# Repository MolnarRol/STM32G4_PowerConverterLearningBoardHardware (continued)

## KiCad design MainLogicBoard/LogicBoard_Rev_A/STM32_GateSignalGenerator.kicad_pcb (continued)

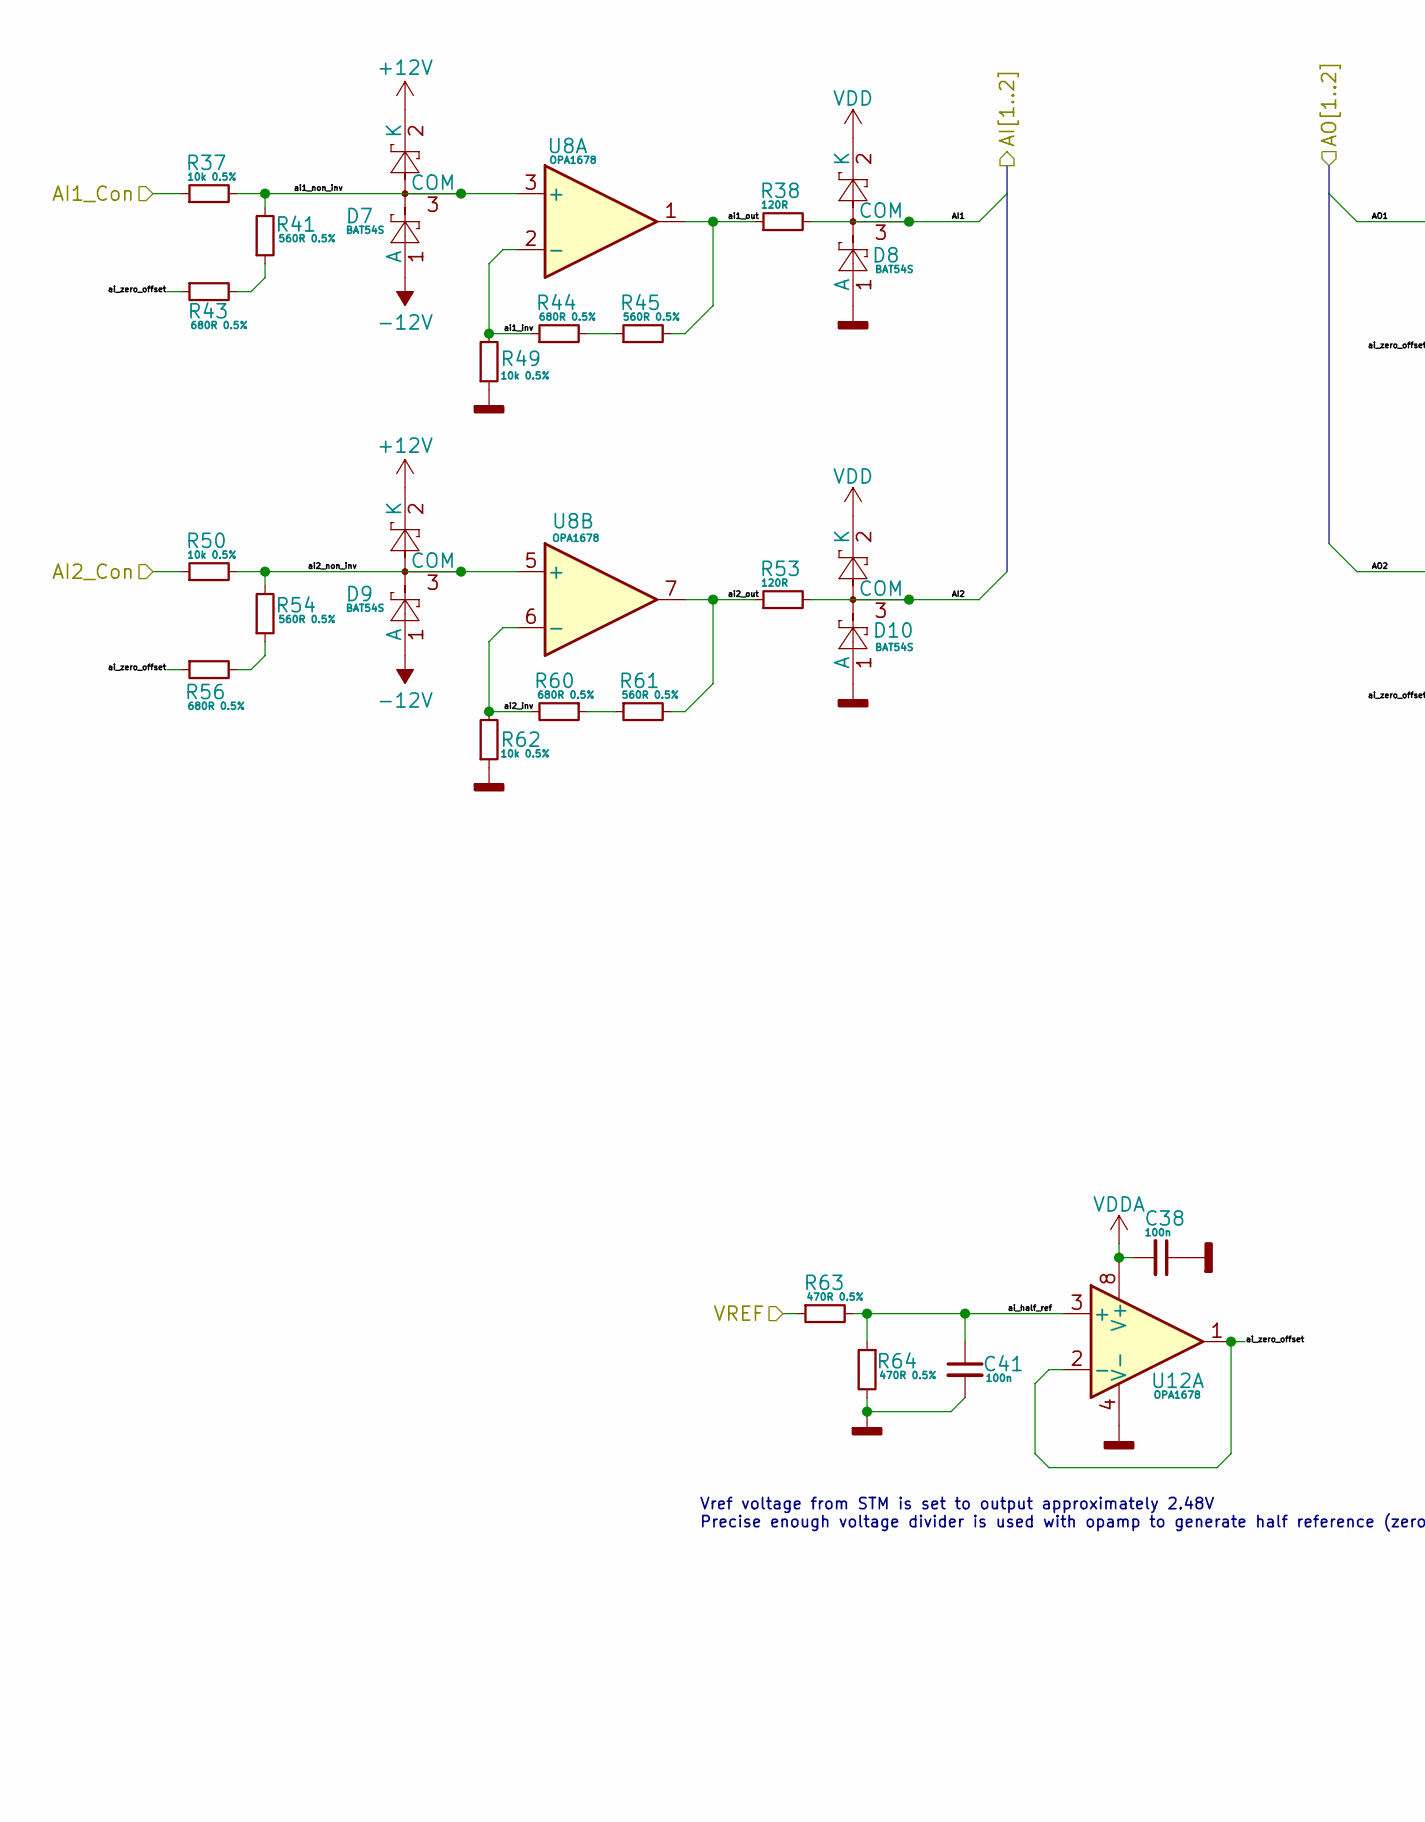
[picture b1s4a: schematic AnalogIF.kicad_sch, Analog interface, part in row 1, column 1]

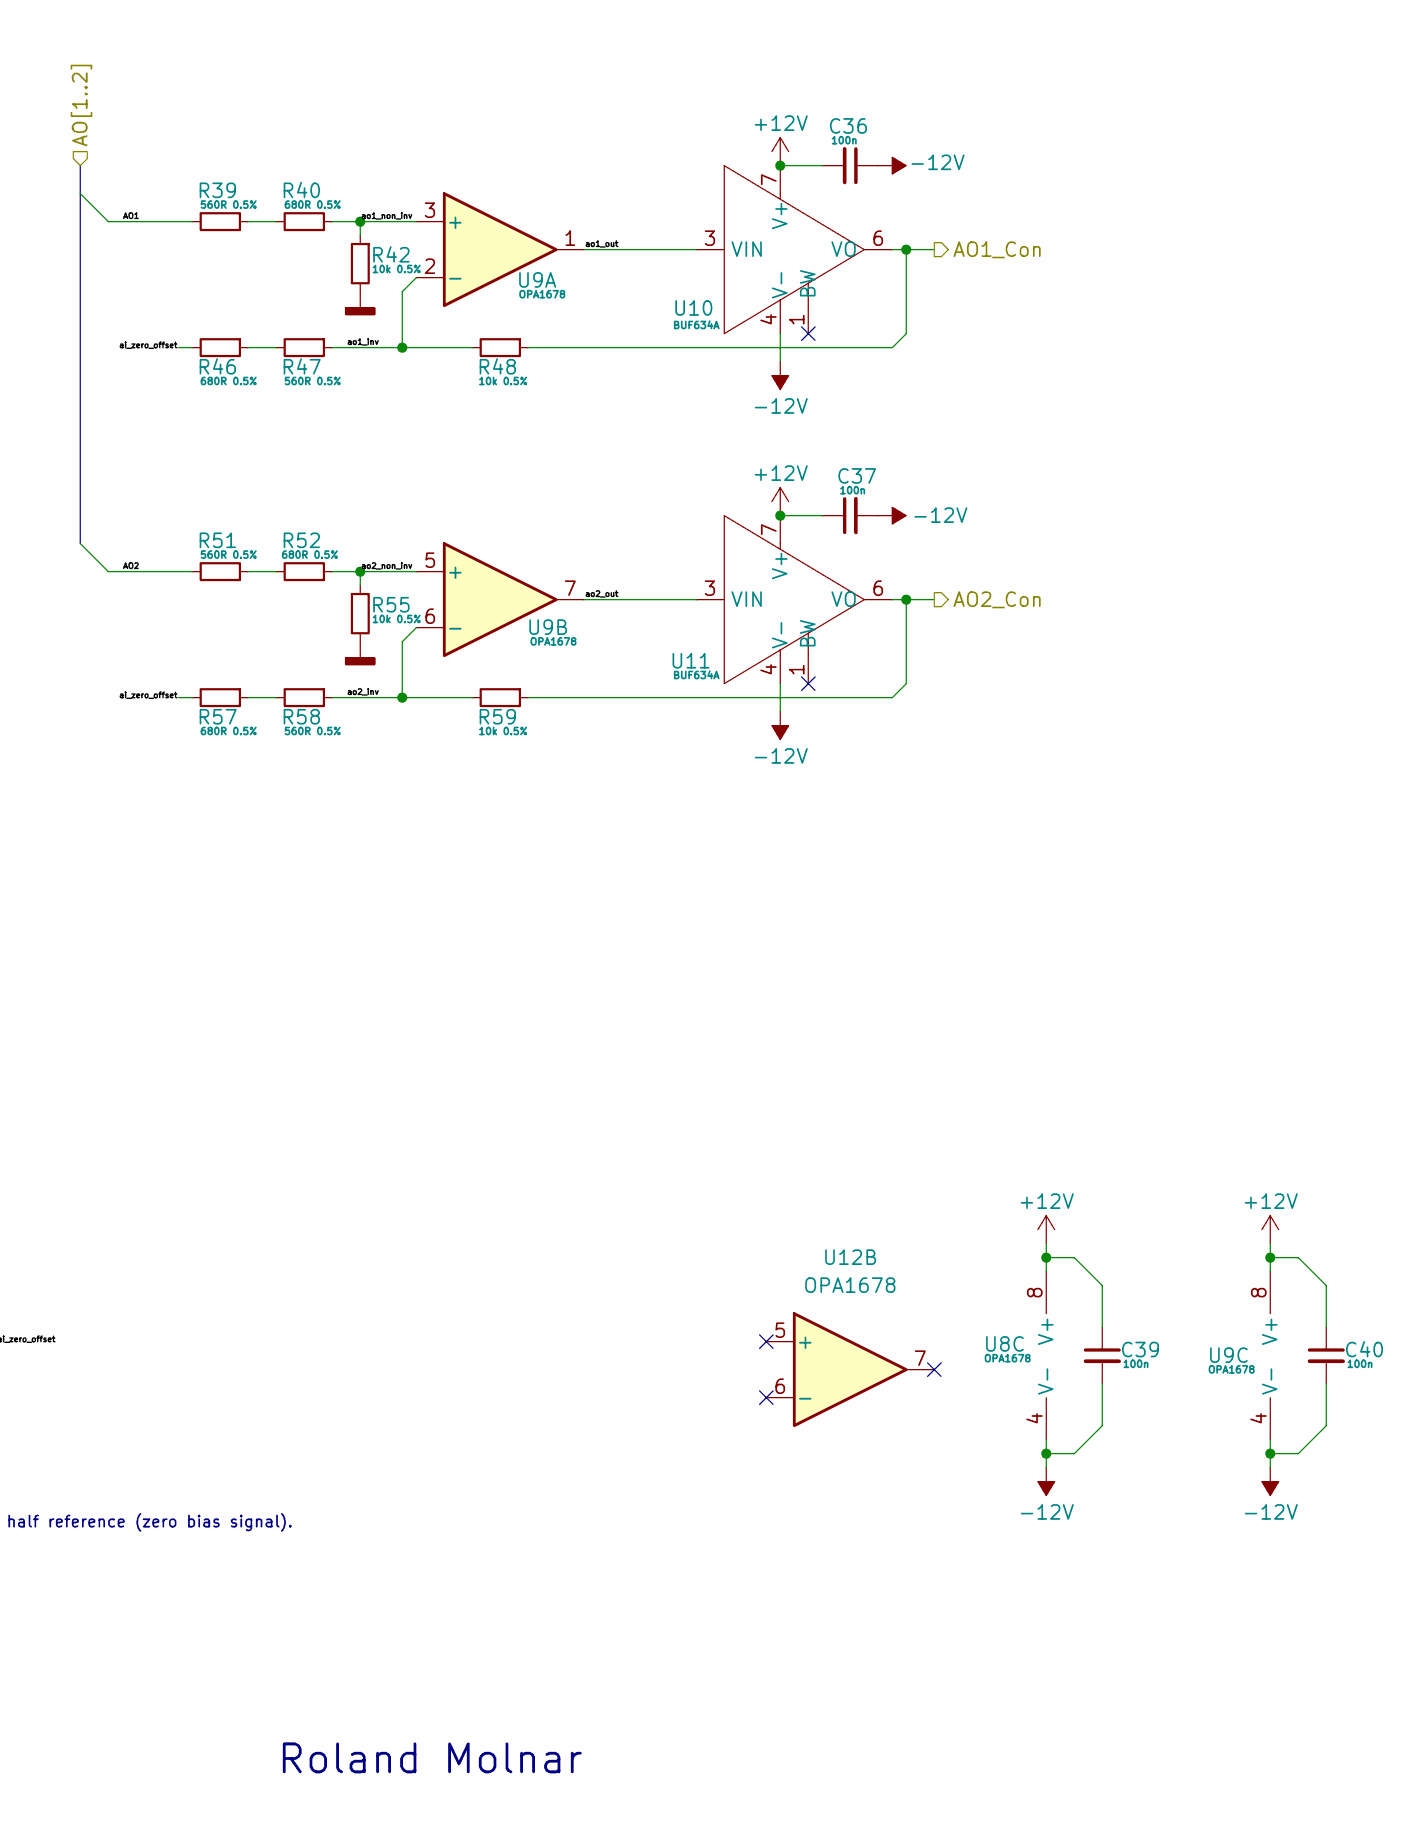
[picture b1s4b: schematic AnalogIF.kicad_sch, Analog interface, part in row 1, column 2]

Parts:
C36, C37, C38, C39, C40, C41: 100n; C_0805_2012Metric; Manufacturer PN C0805C104K5RAC7411; DigiKey PN 399-C0805C104K5RAC7210CT-ND
D7, D8, D9, D10: BAT54S; SOT-23; Manufacturer PN BAT54S; DigiKey PN 4878-BAT54SCT-ND
R37, R42, R48, R49, R50, R55, R59, R62: 10k 0.5%; R_0805_2012Metric; Manufacturer PN RT0805DRD0710KL; DigiKey PN 311-2699-1-ND
R38, R53: 120R; R_0805_2012Metric; Manufacturer PN RC0805FR-07120RL; DigiKey PN 311-120CRCT-ND
R39, R41, R45, R47, R51, R54, R58, R61: 560R 0.5%; R_0805_2012Metric; Manufacturer PN ERJ-PB6D5600V; DigiKey PN P20990CT-ND
R40, R43, R44, R46, R52, R56, R57, R60: 680R 0.5%; R_0805_2012Metric; Manufacturer PN ERJ-PB6D6800V; DigiKey PN P21000CT-ND
R63, R64: 470R 0.5%; R_0805_2012Metric; Manufacturer PN ESR10EZPD4700; DigiKey PN 846-ESR10EZPD4700CT-ND
U8, U9, U12: OPA1678; SOIC-8_3.9x4.9mm_P1.27mm; Manufacturer PN OPA1678IDR; DigiKey PN 296-47347-1-ND
U10, U11: BUF634A; SOIC-8_3.9x4.9mm_P1.27mm; Manufacturer PN BUF634AIDR; DigiKey PN 296-53619-1-ND

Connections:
+12V: C36.2, C37.1, C39.1, C40.1, D7.2 (K), D9.2 (K), U8.8 (V+), U9.8 (V+), U10.7 (V+), U11.7 (V+); also elsewhere on the board
-12V: C36.1, C37.2, C39.2, C40.2, D7.1 (A), D9.1 (A), U8.4 (V-), U9.4 (V-), U10.4 (V-), U11.4 (V-); also elsewhere on the board
/AnalogInterface/AI1: D8.3 (COM), R38.2; also elsewhere on the board
/AnalogInterface/AI1_Con: R37.1; also elsewhere on the board
/AnalogInterface/AI2: D10.3 (COM), R53.2; also elsewhere on the board
/AnalogInterface/AI2_Con: R50.1; also elsewhere on the board
/AnalogInterface/AO1: R39.2; also elsewhere on the board
/AnalogInterface/AO1_Con: R48.1, U10.6 (VO); also elsewhere on the board
/AnalogInterface/AO2: R51.2; also elsewhere on the board
/AnalogInterface/AO2_Con: R59.1, U11.6 (VO); also elsewhere on the board
/AnalogInterface/VREF: R63.1; also elsewhere on the board
/AnalogInterface/ai1_inv: R44.1, R49.2, U8.2 (-)
/AnalogInterface/ai1_non_inv: D7.3 (COM), R37.2, R41.2, U8.3 (+)
/AnalogInterface/ai1_out: R38.1, R45.2, U8.1
/AnalogInterface/ai2_inv: R60.2, R62.2, U8.6 (-)
/AnalogInterface/ai2_non_inv: D9.3 (COM), R50.2, R54.2, U8.5 (+)
/AnalogInterface/ai2_out: R53.1, R61.2, U8.7
/AnalogInterface/ai_half_ref: C41.1, R63.2, R64.1, U12.3 (+)
/AnalogInterface/ai_zero_offset: R43.1, R46.2, R56.1, R57.2, U12.1, U12.2 (-)
/AnalogInterface/ao1_inv: R47.1, R48.2, U9.2 (-)
/AnalogInterface/ao1_non_inv: R40.1, R42.1, U9.3 (+)
/AnalogInterface/ao1_out: U9.1, U10.2 (NC), U10.3 (VIN), U10.5 (NC), U10.8 (NC)
/AnalogInterface/ao2_inv: R58.1, R59.2, U9.6 (-)
/AnalogInterface/ao2_non_inv: R52.1, R55.1, U9.5 (+)
/AnalogInterface/ao2_out: U9.7, U11.2 (NC), U11.3 (VIN), U11.5 (NC), U11.8 (NC)
GNDD: C38.1, C41.2, D8.1 (A), D10.1 (A), R42.2, R49.1, R55.2, R62.1, R64.2, U12.4 (V-); also elsewhere on the board
unnamed: R39.1, R40.2
unnamed: R41.1, R43.2
unnamed: R44.2, R45.1
unnamed: R46.1, R47.2
unnamed: R51.1, R52.2
unnamed: R54.1, R56.2
unnamed: R57.1, R58.2
unnamed: R60.1, R61.1
VDD: D8.2 (K), D10.2 (K); also elsewhere on the board
VDDA: C38.2, U12.8 (V+); also elsewhere on the board

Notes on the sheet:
Roland Molnar
Vref voltage from STM is set to output approximately 2.48V Precise enough voltage divider is used with opamp to generate half reference (zero bias signal).

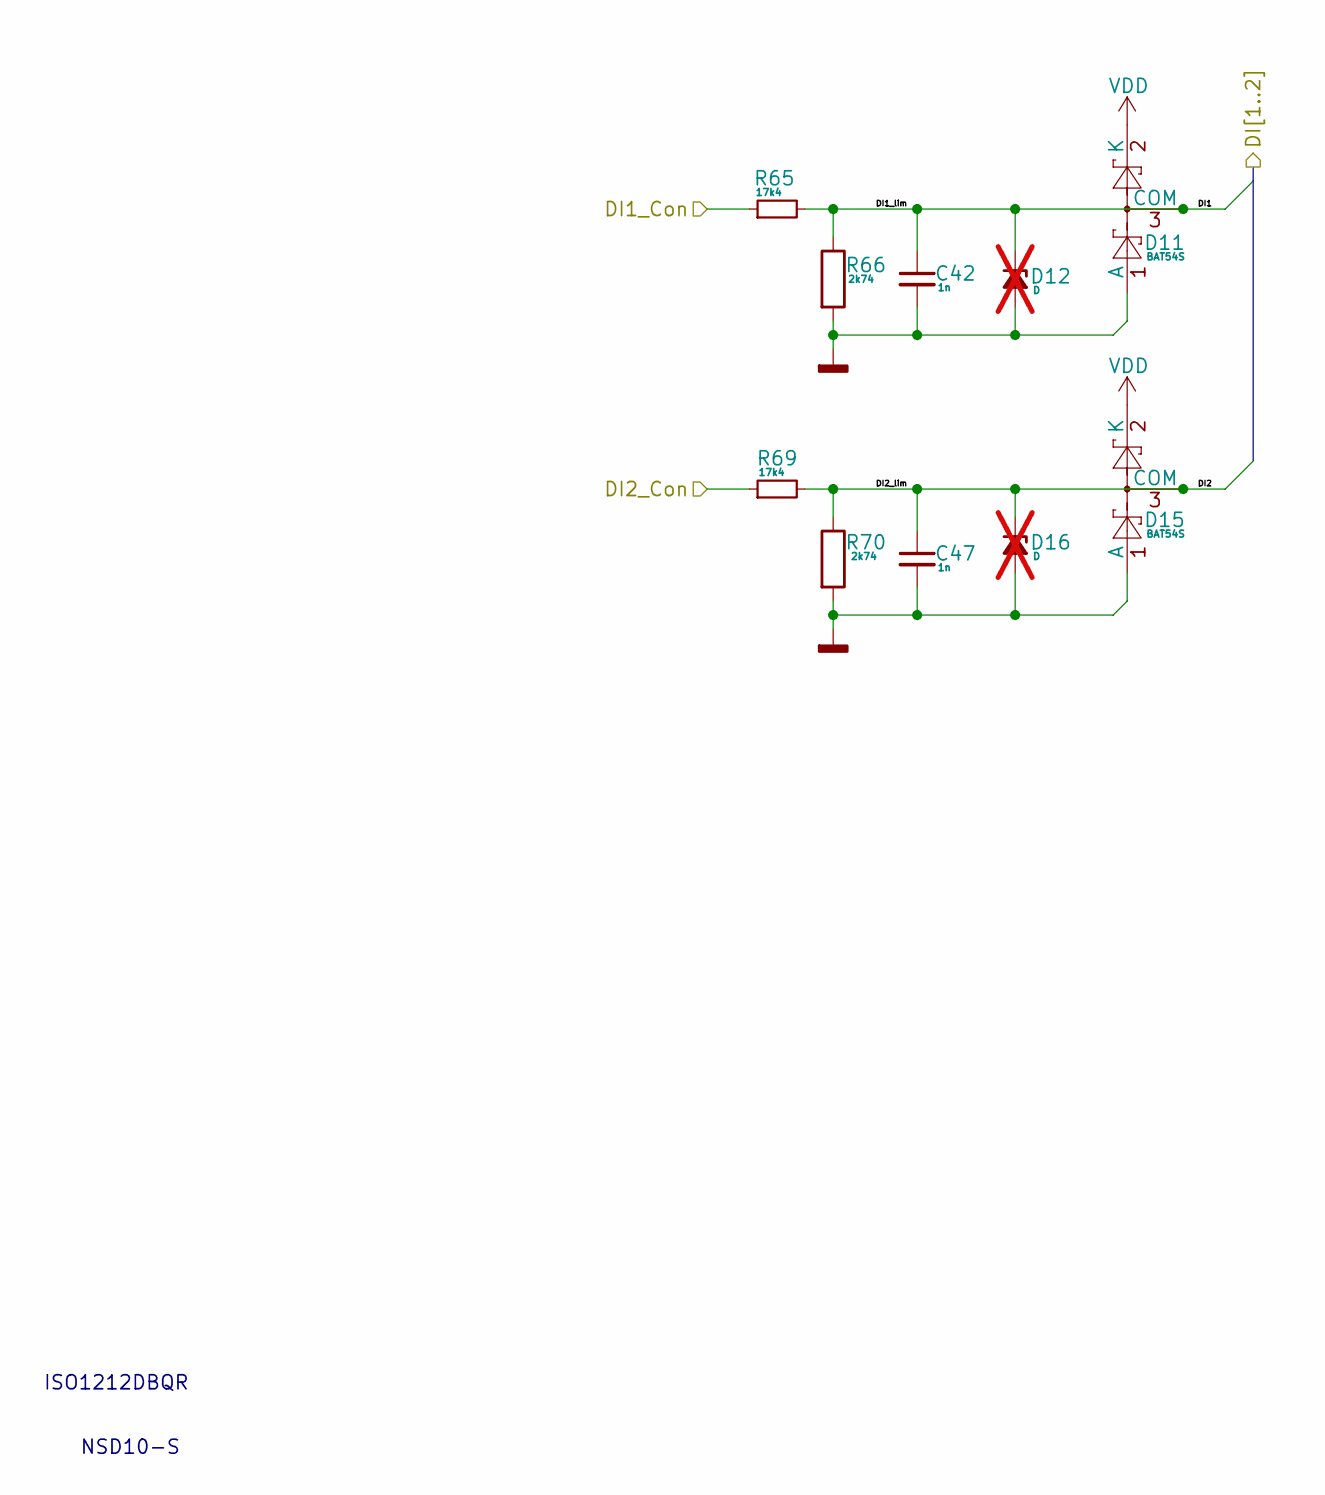
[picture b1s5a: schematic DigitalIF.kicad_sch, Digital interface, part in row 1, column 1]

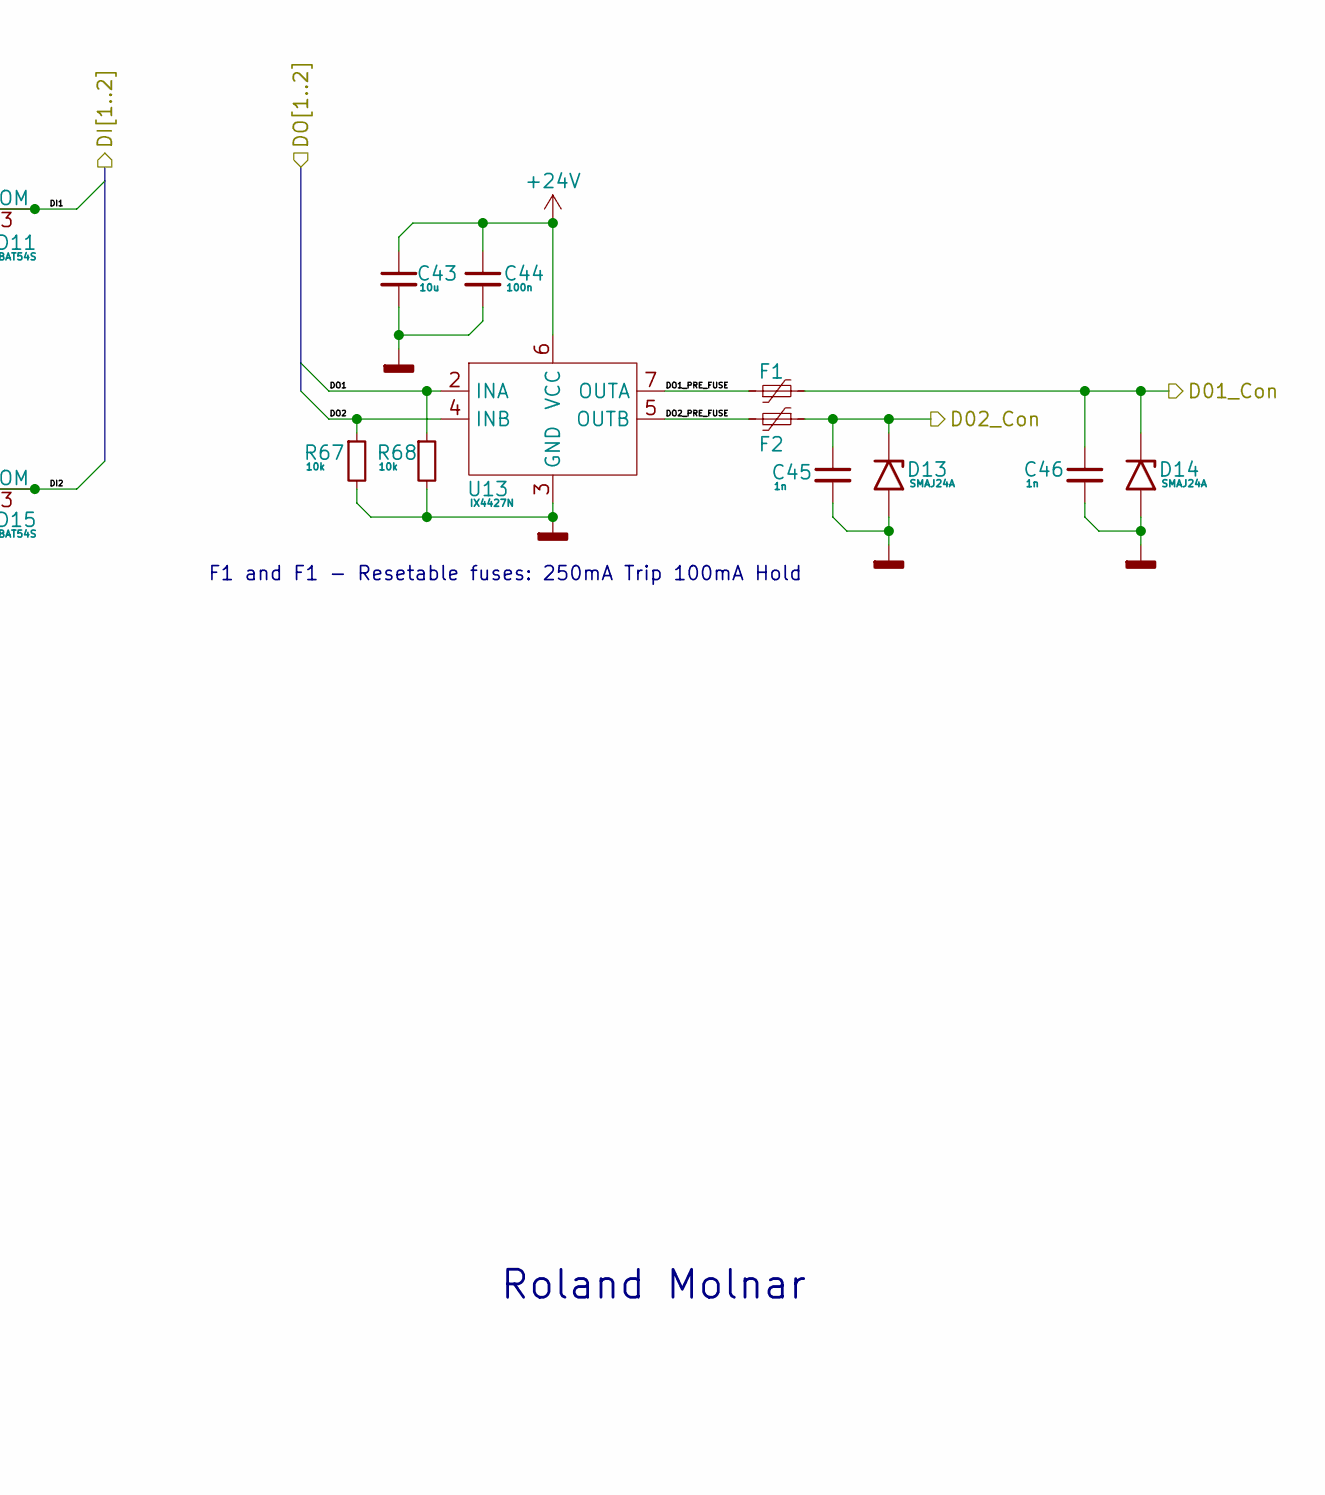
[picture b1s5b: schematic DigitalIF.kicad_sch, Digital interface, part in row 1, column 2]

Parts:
C42, C45, C46, C47: 1n; C_0805_2012Metric; Manufacturer PN C0805C102K5RACTU; DigiKey PN 399-C0805C102K5RACTUCT-ND
C43: 10u; C_0805_2012Metric; Manufacturer PN C0805C106K8PACTU; DigiKey PN 399-C0805C106K8PACTUCT-ND
C44: 100n; C_0805_2012Metric; Manufacturer PN C0805C104K5RAC7411; DigiKey PN 399-C0805C104K5RAC7210CT-ND
D11, D15: BAT54S; SOT-23; Manufacturer PN BAT54S; DigiKey PN 4878-BAT54SCT-ND
D12, D16: D; D_SOD-123; not fitted
D13, D14: SMAJ24A; D_SMA; Manufacturer PN SMAJ24A; DigiKey PN SMAJ24ALFCT-ND
F1, F2: 250mA Trip 100mA Hold; Fuse_1210_3225Metric; Manufacturer PN MICROSMD010F-2; DigiKey PN MICROSMD010F-2CT-ND
R65, R69: 17k4; R_0805_2012Metric; Manufacturer PN RC0805FR-0717K4L; DigiKey PN 311-17.4KCRCT-ND
R66, R70: 2k74; R_0805_2012Metric; Manufacturer PN RC0805FR-072K74L; DigiKey PN 311-2.74KCRCT-ND
R67, R68: 10k; R_0805_2012Metric; Manufacturer PN RT0805DRD0710KL; DigiKey PN 311-2699-1-ND
U13: IX4427N; SOIC-8_3.9x4.9mm_P1.27mm; Manufacturer PN IX4427N; DigiKey PN 5656-IX4427N-ND

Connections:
+24V: C43.1, C44.1, U13.6 (VCC); also elsewhere on the board
/DigitalInterface/D01_Con: C46.1, D14.1 (A1), F1.2; also elsewhere on the board
/DigitalInterface/D02_Con: C45.1, D13.1 (A1), F2.1; also elsewhere on the board
/DigitalInterface/DI1: C42.1, D11.3 (COM), D12.1 (K), R65.2, R66.1; also elsewhere on the board
/DigitalInterface/DI1_Con: R65.1; also elsewhere on the board
/DigitalInterface/DI2: C47.1, D15.3 (COM), D16.1 (K), R69.2, R70.1; also elsewhere on the board
/DigitalInterface/DI2_Con: R69.1; also elsewhere on the board
/DigitalInterface/DO1: R68.1, U13.2 (INA); also elsewhere on the board
/DigitalInterface/DO1_PRE_FUSE: F1.1, U13.7 (OUTA)
/DigitalInterface/DO2: R67.1, U13.4 (INB); also elsewhere on the board
/DigitalInterface/DO2_PRE_FUSE: F2.2, U13.5 (OUTB)
GNDD: C42.2, C43.2, C44.2, C45.2, C46.2, C47.2, D11.1 (A), D12.2 (A), D13.2 (A2), D14.2 (A2), D15.1 (A), D16.2 (A), R66.2, R67.2, R68.2, R70.2, U13.3 (GND); also elsewhere on the board
VDD: D11.2 (K), D15.2 (K); also elsewhere on the board

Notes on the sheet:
F1 and F1 - Resetable fuses: 250mA Trip 100mA Hold
Roland Molnar
ISO1212DBQR
NSD10-S

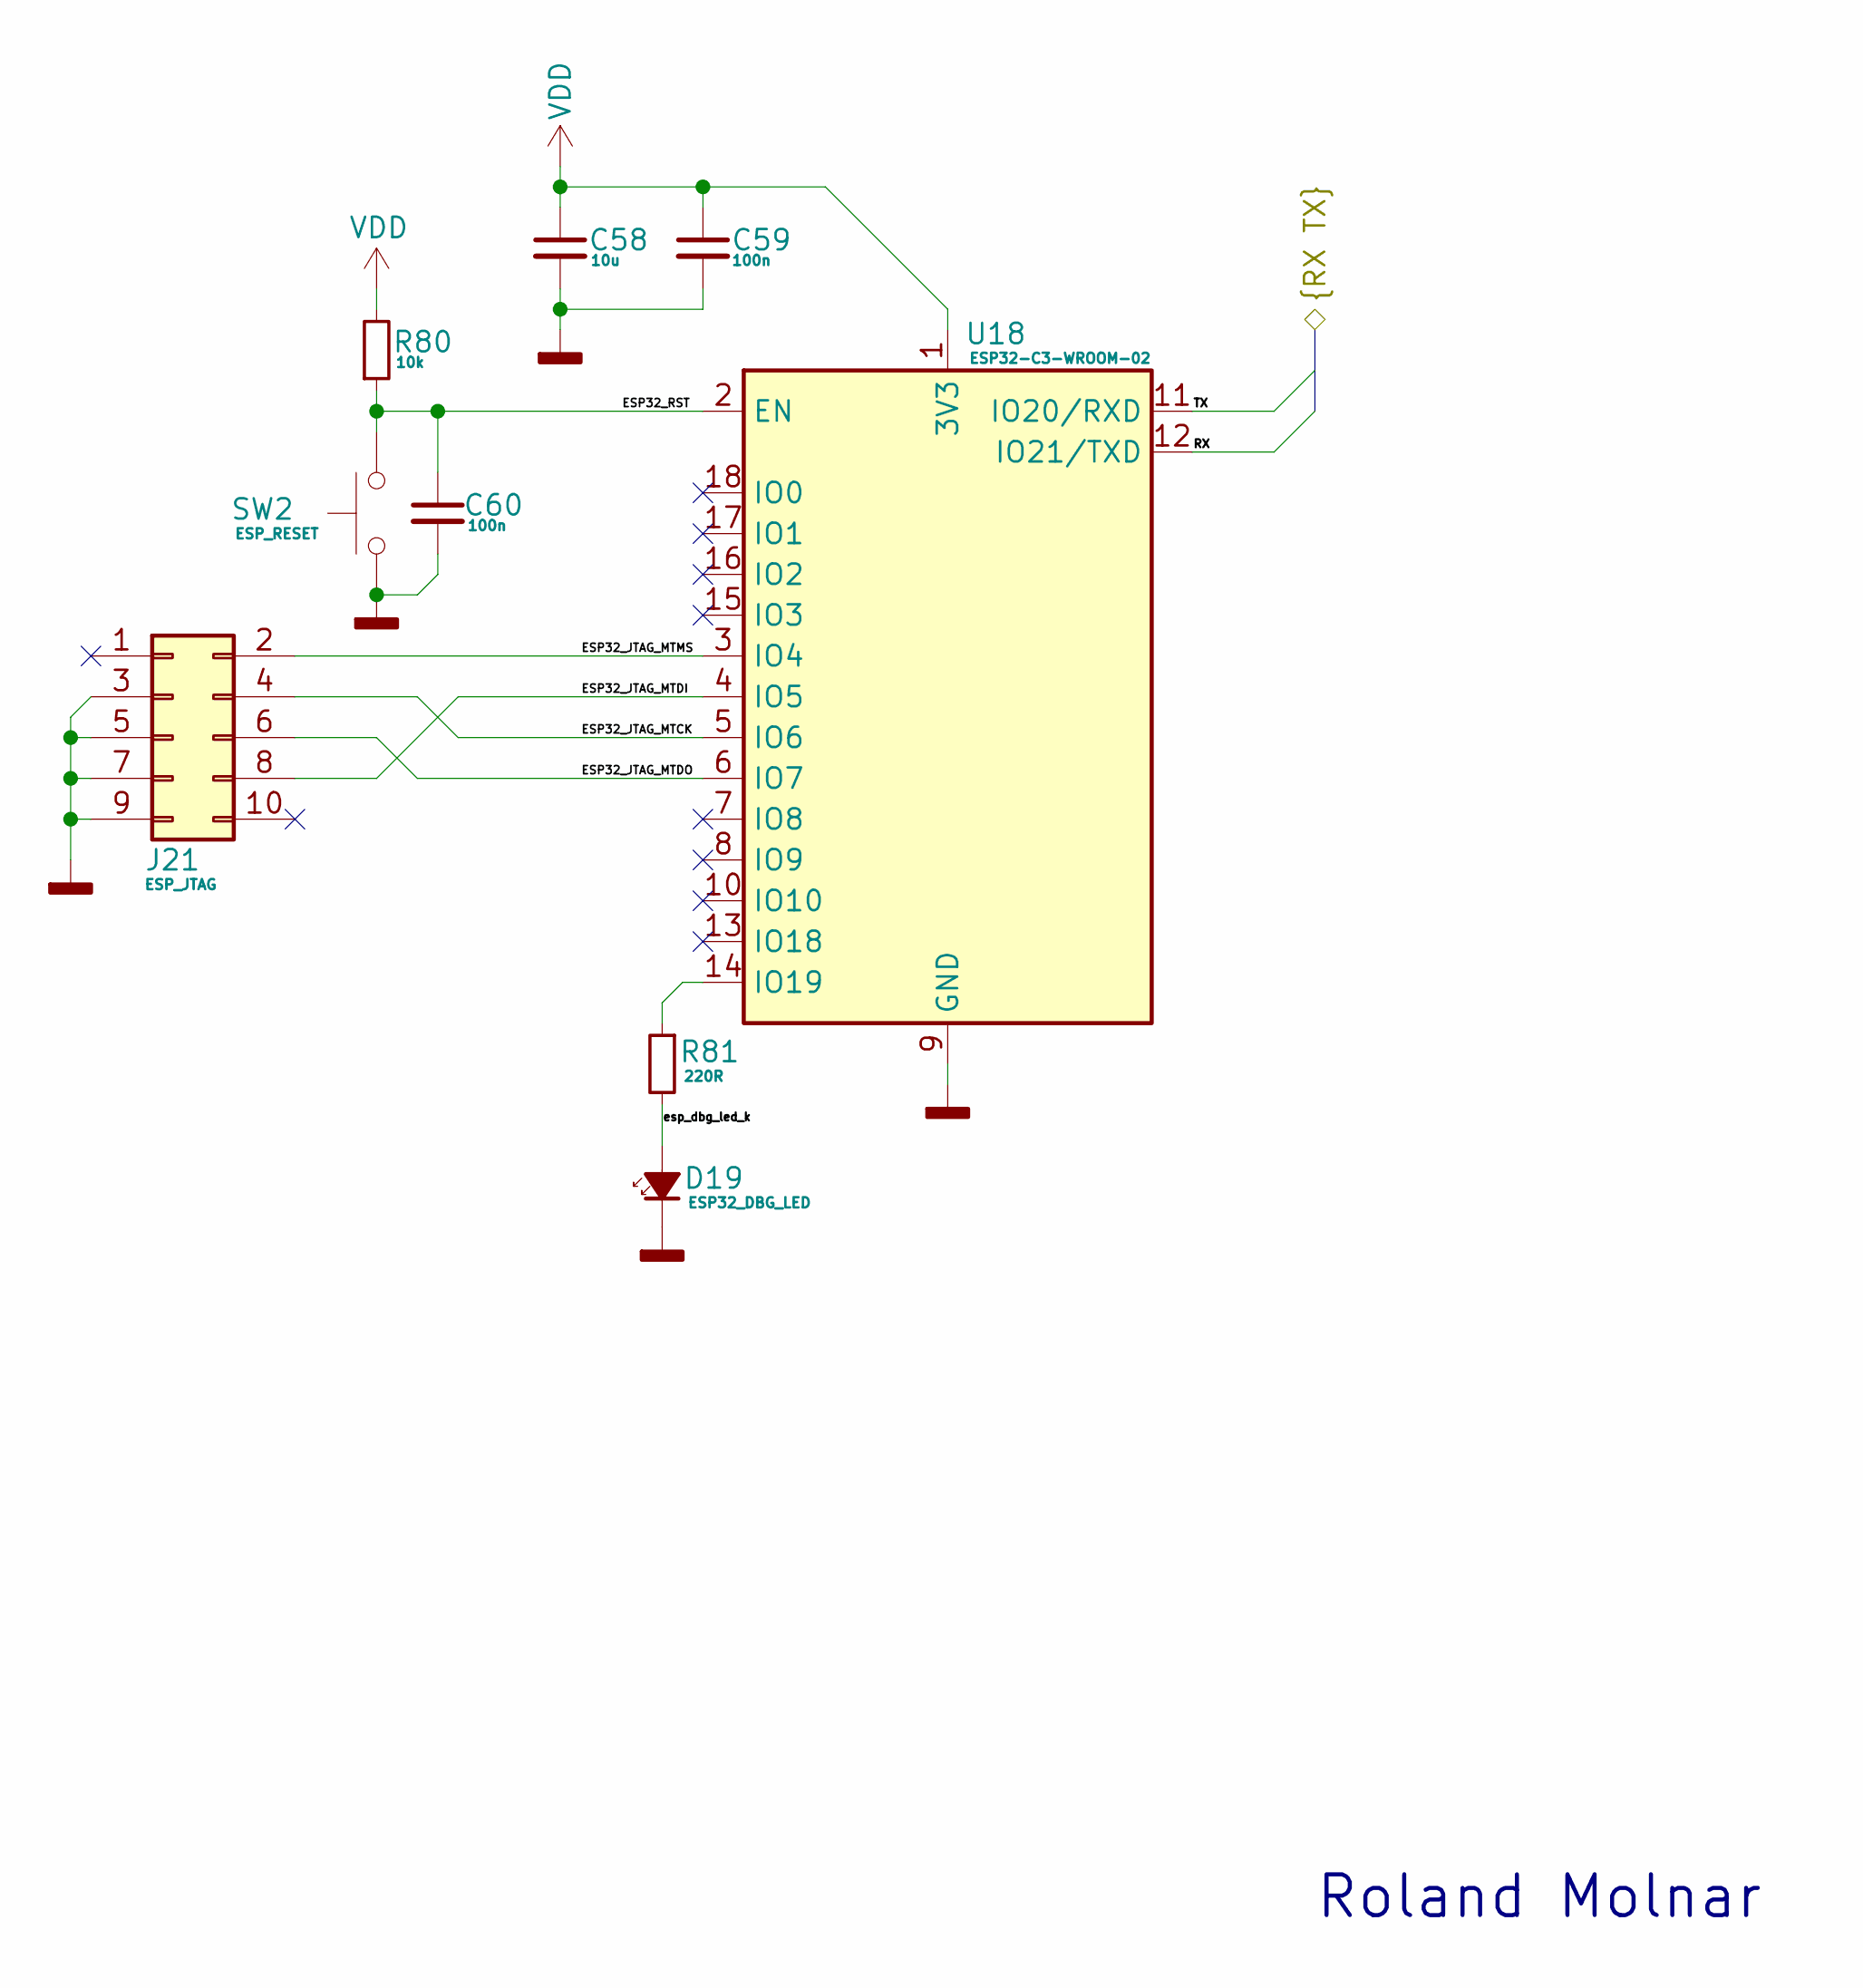
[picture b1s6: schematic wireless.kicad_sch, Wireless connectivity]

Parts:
C58: 10u; C_0805_2012Metric; Manufacturer PN C0805C106K8PACTU; DigiKey PN 399-C0805C106K8PACTUCT-ND
C59, C60: 100n; C_0805_2012Metric; Manufacturer PN C0805C104K5RAC7411; DigiKey PN 399-C0805C104K5RAC7210CT-ND
D19: ESP32_DBG_LED; LED_0805_2012Metric; Manufacturer PN LTST-C171KRKT; DigiKey PN 160-1427-1-ND
J21: ESP_JTAG; PinHeader_2x05_P1.27mm_Vertical; Manufacturer PN FTSH-105-01-L-D-K; DigiKey PN SAM8798-ND
R80: 10k; R_0805_2012Metric; Manufacturer PN RT0805DRD0710KL; DigiKey PN 311-2699-1-ND
R81: 220R; R_0805_2012Metric; Manufacturer PN RC0805FR-07220RL; DigiKey PN 311-220CRCT-ND
SW2: ESP_RESET; SW_SPST_PTS647_Sx38; Manufacturer PN PTS647SN50SMTR2 LFS; DigiKey PN PTS647SN50SMTR2LFSCT-ND
U18: ESP32-C3-WROOM-02; Manufacturer PN ESP32-C3-WROOM-02-H4; DigiKey PN 1965-ESP32-C3-WROOM-02-H4CT-ND

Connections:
/Uart.RX: U18.12 (IO21/TXD); also elsewhere on the board
/Uart.TX: U18.11 (IO20/RXD); also elsewhere on the board
/Wireless connectivity - ESP32/ESP32_JTAG_MTCK: J21.4, U18.5 (IO6)
/Wireless connectivity - ESP32/ESP32_JTAG_MTDI: J21.8, U18.4 (IO5)
/Wireless connectivity - ESP32/ESP32_JTAG_MTDO: J21.6, U18.6 (IO7)
/Wireless connectivity - ESP32/ESP32_JTAG_MTMS: J21.2, U18.3 (IO4)
/Wireless connectivity - ESP32/ESP32_RST: C60.1, R80.1, SW2.2, U18.2 (EN)
/Wireless connectivity - ESP32/esp_dbg_led_k: D19.2 (A), R81.2
GNDD: C58.2, C59.2, C60.2, D19.1 (K), J21.3, J21.5, J21.7, J21.9, SW2.1, U18.9 (GND), U18.19 (GND); also elsewhere on the board
unnamed: R81.1, U18.14 (IO19)
VDD: C58.1, C59.1, R80.2, U18.1 (3V3); also elsewhere on the board

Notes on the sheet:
Roland Molnar

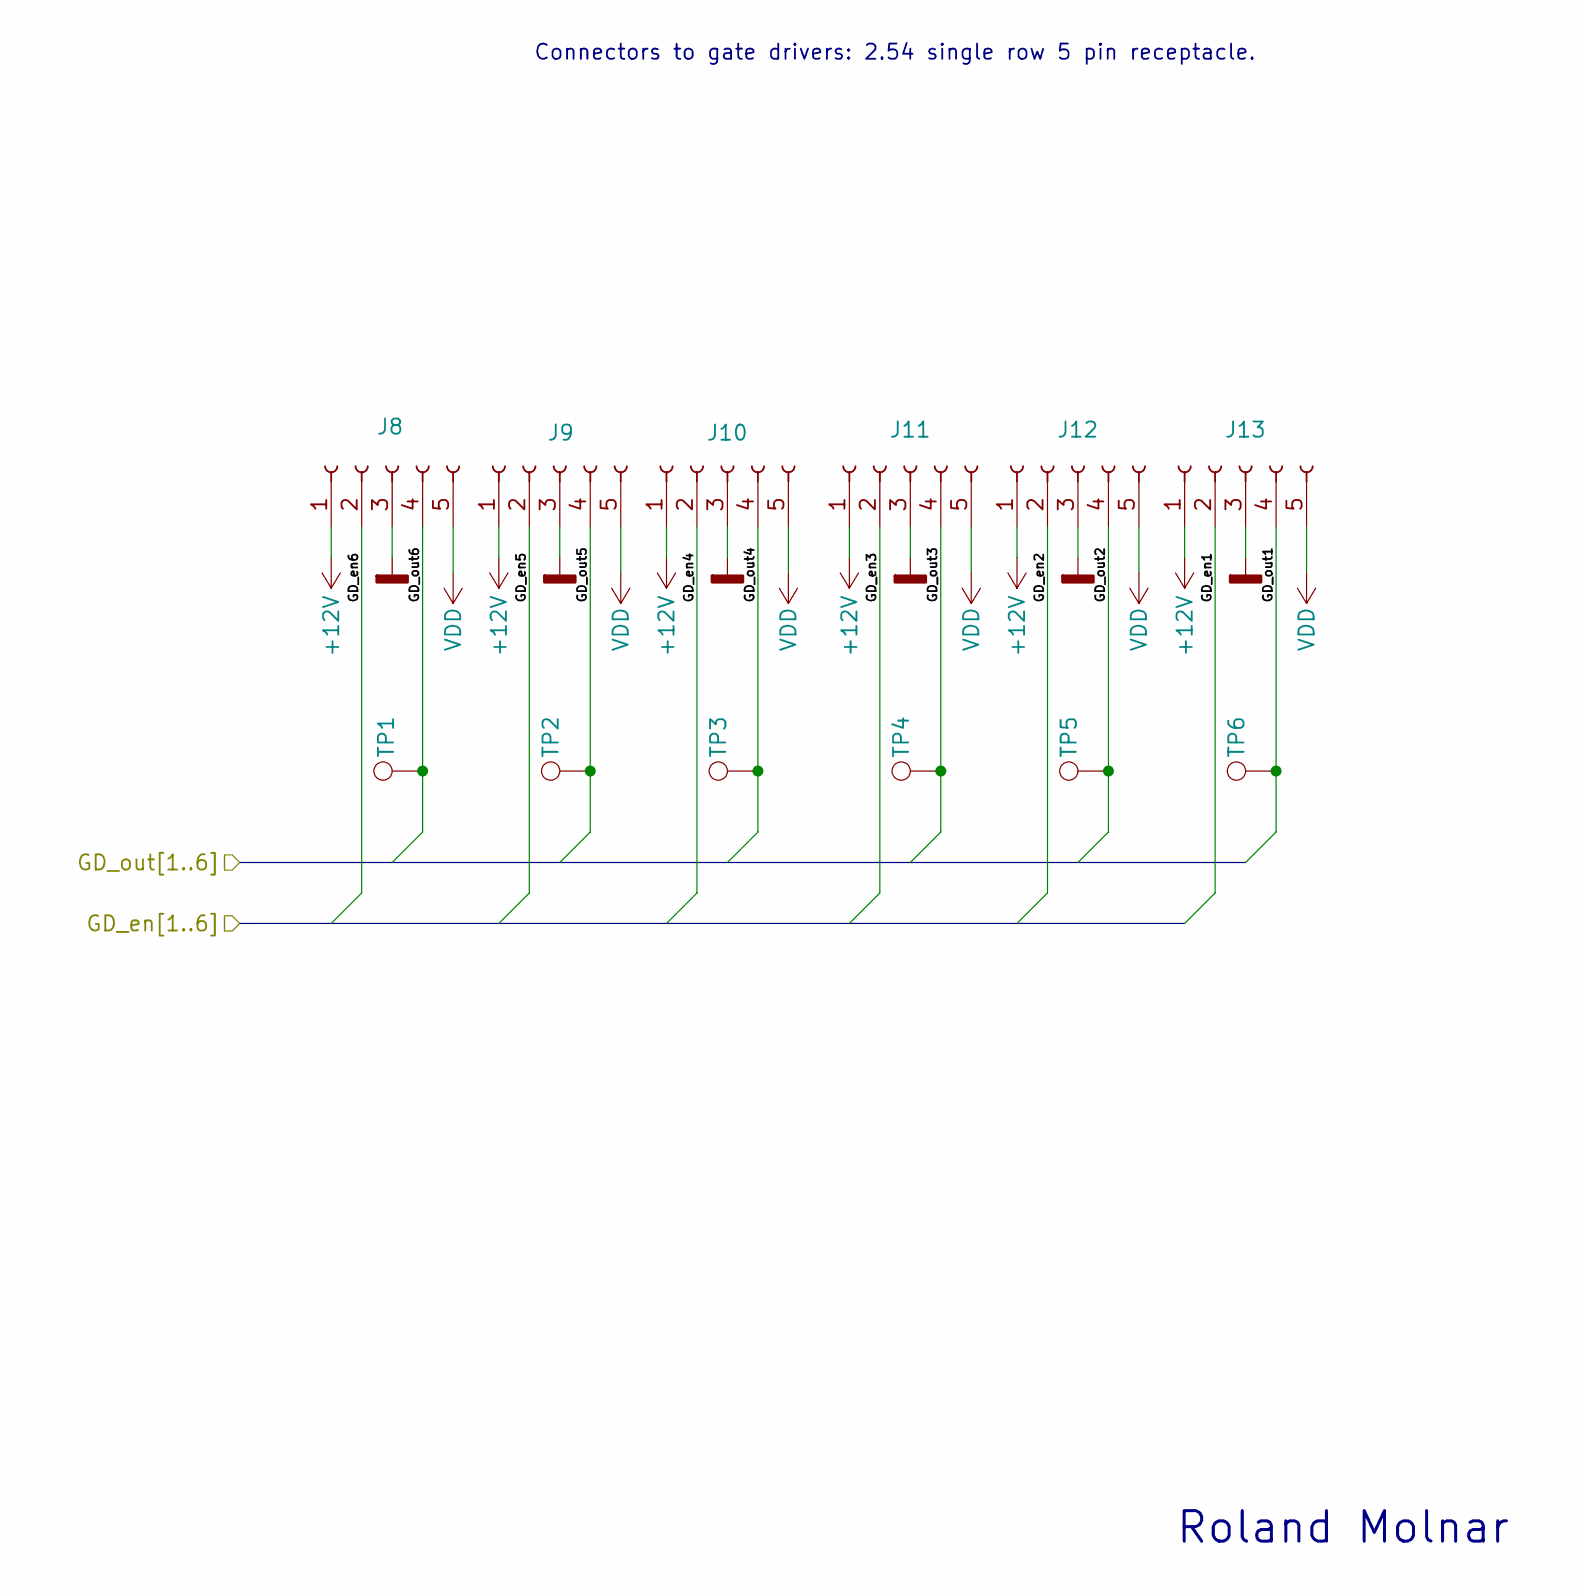
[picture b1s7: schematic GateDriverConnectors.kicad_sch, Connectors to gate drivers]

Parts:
J8, J9, J10, J11, J12, J13: Pin socket 2.54mm 1x5 90 deg; PinSocket_1x05_P2.54mm_Horizontal; Manufacturer PN SSW-105-02-F-S-RA; DigiKey PN 612-SSW-105-02-F-S-RA-ND
TP1, TP2, TP3, TP4, TP5, TP6: Keystone 5009 (Yellow); TestPoint_Keystone_5005-5009_Compact; Manufacturer PN 5009; DigiKey PN 36-5009-ND

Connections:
+12V: J8.1, J9.1, J10.1, J11.1, J12.1, J13.1; also elsewhere on the board
/Gate driver connectors/GD_en1: J13.2; also elsewhere on the board
/Gate driver connectors/GD_en2: J12.2; also elsewhere on the board
/Gate driver connectors/GD_en3: J11.2; also elsewhere on the board
/Gate driver connectors/GD_en4: J10.2; also elsewhere on the board
/Gate driver connectors/GD_en5: J9.2; also elsewhere on the board
/Gate driver connectors/GD_en6: J8.2; also elsewhere on the board
/Gate driver connectors/GD_out1: J13.4, TP6.1; also elsewhere on the board
/Gate driver connectors/GD_out2: J12.4, TP5.1; also elsewhere on the board
/Gate driver connectors/GD_out3: J11.4, TP4.1; also elsewhere on the board
/Gate driver connectors/GD_out4: J10.4, TP3.1; also elsewhere on the board
/Gate driver connectors/GD_out5: J9.4, TP2.1; also elsewhere on the board
/Gate driver connectors/GD_out6: J8.4, TP1.1; also elsewhere on the board
GNDD: J8.3, J9.3, J10.3, J11.3, J12.3, J13.3; also elsewhere on the board
VDD: J8.5, J9.5, J10.5, J11.5, J12.5, J13.5; also elsewhere on the board

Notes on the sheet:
Connectors to gate drivers: 2.54 single row 5 pin receptacle.
Roland Molnar
